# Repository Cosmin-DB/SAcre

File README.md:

# SAcre / SmartFeedbackDevice

Diseño electrónico de un dispositivo portátil basado en ESP32.

- Autor: Cosmin Dobrescu
- Herramienta: KiCad 10
- Proyecto principal: `sacre.kicad_pro`
- Estado: esquema y PCB corregidos; revisión digital completada (2026-09-13).
  Pendientes: aprobación física final, preparación del pedido y pruebas del prototipo.

## Mecanismo de trabajo

1. Leer este archivo completo antes de continuar una revisión.
2. Usar este README como única fuente de verdad. Las hipótesis nuevas del
   asistente se mantienen únicamente en `REVISION_PROVISIONAL.md` hasta que el
   autor las acepte o descarte; no crear otros informes auxiliares.
3. Mantener un identificador estable para cada incidencia.
4. Tratar toda incidencia inicialmente como una hipótesis, no como un fallo
   confirmado.
5. Intentar refutarla contrastando esquemático, PCB, símbolo, huella, datasheet
   y, cuando exista, evidencia del prototipo.
6. Registrar únicamente:
   - `Hipótesis`: afirmación que se comprueba.
   - `Evidencia`: datos concretos que sostienen el dictamen.
   - `Acción`: cambio exacto, solo si procede.
   - `Cierre`: comprobación necesaria para darlo por válido.
7. Usar estos estados:
   `PENDIENTE → CONFIRMADO / DESCARTADO / CONDICIONAL → CORREGIDO → VALIDADO`.
8. Durante la verificación no modificar el diseño.
9. La preparación de PCB autorizada el 2026-09-13 ya se completó. El enrutado
   y ajuste físico quedan al autor; cualquier nueva modificación de PCB por
   el asistente requiere un alcance autorizado. Comparar antes/después y no
   alterar cobre, contorno, conectores o keepout fuera de ese alcance.
10. Registrar por separado en cada incidencia:
    - `[ ] Esquemático corregido`
    - `[ ] PCB corregida y revisada por el autor`
11. Corregir únicamente incidencias `CONFIRMADO`; no corregir las
    `CONDICIONAL` sin resolver antes su condición.
12. Marcar `VALIDADO` solo después de aplicar el criterio de cierre y las
    comprobaciones ERC/DRC pertinentes.
13. Mantener separadas las mejoras preventivas de los fallos demostrados.
14. Evitar duplicar información y conservar las entradas breves, verificables
    y comprensibles sin contexto externo.
15. No volver a listar como trabajo pendiente una corrección ya aplicada.
    Distinguir revisión digital, aprobación del autor y prueba física; los
    datos de versiones antiguas deben identificarse como históricos.

## Fuentes para la verificación

Los datasheets recopilados están en `documentation/datasheets/`; se conservan
también los documentos útiles que ya estaban en `documentation/` y `RV-8803/`.
`bom_jlcpb.csv` identifica las piezas del prototipo anterior: sirve para
investigar sus fallos, no para pedir la nueva placa. Para fabricar, generar
el BOM desde el diseño actual usando sus campos `LCSC Part #`; ni los BOM
históricos ni las tablas resumidas de este documento sustituyen esa exportación.

| Bloque | Referencias cubiertas | Estado |
| --- | --- | --- |
| MCU y RF | ESP32-PICO-D4, guía de hardware ESP32, AN012400C00R3200 | Completo |
| Pantalla y táctil | GDEY042T81-T02, SSD1683, FT6336U, AFC24-S06FIC-00, AFC24-S24FIA-00 | Completo |
| USB, sensores y mando | CP2104, conector USB-C, LIS3DH, RV-8803-C7, pulsador | Completo |
| Alimentación y protección | TLV62568, TP4054, FHD4020S-470MT, FTC252012S1R0MBCA, BAT54C, MBR0530, SP0503BAHTG | Completo |
| Transistores y motor | CJ2312, CJ3415, SI1308EDL, UMH3N, S8050 | Completo para los componentes montados |

Selección actual de referencias críticas (incluye las sustituciones del prototipo):

| Ref. | Pieza seleccionada | LCSC |
| --- | --- | --- |
| Q2 | R+O S8050 | C20069125 |
| U5 | JSMSEMI TP4054 | C5381776 |
| L1 | cjiang FHD4020S-470MT | C843300 |
| L3 | cjiang FTC252012S1R0MBCA | C5832370 |
| Q4 | TECH PUBLIC SI1308EDL | C7603347 |
| D1, D8, D9 | JSCJ MBR0530 | C77336 |
| D2–D4 | onsemi MBR0530T3G | C236079 |
| D5 | R+O BAT54C | C22466350 |

Los documentos de MCP73831 y LQH44PN quedan solo como comparación: no
describen los componentes seleccionados para la nueva fabricación.

Auditoría de campos de compra: **85 componentes, 39 códigos distintos** con
`LCSC Part #` idéntico en esquema y PCB, incluida R28=`C21190` como R11.
No se añaden alias duplicados: Fabrication Toolkit, instalado en este equipo,
lee ese campo y lo exporta junto a `Designator`, `Footprint`, `Quantity` y
`Value`. Sincronizar esquema y PCB antes de exportar; comprobar códigos y
orientaciones en la previsualización de JLCPCB, no sólo la detección automática.
Chequeo del exportador y propuestas no aplicadas de reducción de variedad:
`REVISION_PROVISIONAL.md`, sección «BOM y posiciones de montaje» (2026-09-14).
Fuentes: [atributos del exportador](https://github.com/bennymeg/Fabrication-Toolkit#attributes)
y [guía KiCad de JLCPCB](https://jlcpcb.com/help/article/how-to-generate-the-bom-and-centroid-file-from-kicad).

H1–H4, J5, J6 y TP1 son elementos de PCB, sin referencia de compra y excluidos
del BOM. M1 se compra por AliExpress: excluido del BOM y del archivo de
posiciones de montaje en esquema y PCB; su huella y conexiones se conservan.
Quedan por confirmar modelo, corriente de arranque y encaje del motor.

Preparación del pedido (2026-09-14): JLCPCB emparejó correctamente las 85
referencias con los 39 códigos previstos para **4 placas ensambladas**. U2,
ESP32-PICO-D4 `C193707`, está clasificado como `Standard Only`, por lo que el
pedido debe usar **Standard PCBA, cara superior**. La propuesta de sustituir
R23/R24 por valores ya presentes reduciría dos alimentadores, pero fue
descartada por el autor: se conservan 24 kΩ/47 kΩ y 39 códigos. En la
previsualización, el autor corrigió manualmente sólo la orientación de Y1;
comprobarla otra vez en cualquier pedido futuro.

Stock consultado en la biblioteca de montaje JLCPCB el 2026-09-13:
39 referencias con existencias. AE1 tenía 8 unidades, pero el autor dispone
de acopio propio; Y1 tenía 2 y se acepta omitir el RTC si falta. SW1 tenía
970 unidades, cantidad aceptada por el autor. Reconfirmar disponibilidad al
pedir: la consulta no reserva piezas ni el stock de LCSC garantiza montaje
inmediato en JLCPCB. Preparar el pedido teniendo en cuenta el acopio y las
omisiones acordadas; no se ha cambiado ningún campo DNP del diseño.

## Fallos observados en el prototipo

Las correcciones indicadas ya están aplicadas al esquema y a la PCB.
Las casillas de aprobación del autor y las pruebas físicas siguen abiertas;
no significan que falte repetir el enrutado. La evidencia del fallo describe
la primera placa fabricada, no la versión actual.

- [ ] `TOUCH-01` SDA y SCL intercambiadas en el FPC táctil.
  - [x] Esquemático corregido: J1.1=`SCL` y J1.2=`SDA`.
  - [ ] PCB corregida y revisada por el autor.
  - `Estado`: CORREGIDO EN ESQUEMA Y PCB; prueba del táctil pendiente.
  - `Cierre`: comprobar detección del FT6336U y niveles/flancos de ambas
    señales con el flex conectado.
- [ ] `TOUCH-02` Revisar holgura, orientación y salida del flex táctil.
- [ ] `MOTOR-01` Incompatibilidad entre el pinout de Q2 y su huella.
  - [x] Esquemático corregido: Q2 es el S8050 SOT-23 montado, B1/E2/C3
    (`C20069125`).
  - [ ] PCB corregida y revisada por el autor.
  - `Estado`: CORREGIDO EN ESQUEMA Y PCB; validación del motor pendiente.
- [x] `TOUCH-03` Pull-up de la interrupción táctil descartado.
  - `Estado`: DESCARTADO; `INT_TOUCH` puede permanecer en GPIO35.
  - `Evidencia`: el FT6336U declara `INT` como E/S CMOS y no prescribe un
    pull-up externo. Verificar por medida sólo si aparecen flancos inestables.
- [ ] `PWR-02` El USB provoca arranque y ciclos rápidos de encendido/apagado.
  - `Estado`: CORREGIDO EN ESQUEMA Y PCB; validación del encendido pendiente.
  - `Hipótesis`: en el diseño fabricado U3 queda alimentado directamente por
    `USB_VBUS` mientras U2 está apagado. `TXD` llega sin aislamiento a `U0RXD`
    y `DTR/RTS` cruzan
    también hacia `EN/GPIO0` mediante Q7; cualquiera de esas vías puede
    realimentar parcialmente el ESP32 y `+3V3`. Esa tensión puede activar
    IO25/Q6 y el latch. Al caer de nuevo la alimentación, el USB repite el
    proceso.
  - `Evidencia`: en el diseño fabricado U3 está configurado como bus-powered;
    `TXD` y `U0RXD` están unidos directamente. Q7 contiene resistencias de base
    internas de 4,7 kΩ,
    pero no aísla un dominio alimentado de otro apagado. IO25 controla la
    puerta de Q6 mediante R18, Q6 tiene un umbral de 0,45–1 V y R14 sólo lo
    descarga con 100 kΩ. R13/C18 forman una constante de 30 ms. L2 puede
    agravar la caída, pero no explica el disparo inicial desde USB.
  - `Decisión`: U3 queda self-powered físicamente. `VDD`, `VIO` y `REGIN` van
    a `+3V3`; R23/R24=24 kΩ/47 kΩ detectan `USB_VBUS` sin realimentación;
    C23=1 µF y C20=0,1 µF desacoplan U3. C17=1 µF mejora `EN`.
    R13/C18 permanecen en 300 kΩ/100 nF; no se añade supervisor ni histéresis.
    El firmware debe activar IO25 pronto y puede exigir mantener el pulsador
    durante la programación.
  - `Cierre`: al conectar USB con el latch apagado, observar `VSYS`, `+3V3`,
    puerta de Q6 y puerta de Q5. Si `+3V3` sube antes que `VSYS`, queda
    confirmada la realimentación desde U3; repetir aislando `TXD` o forzando
    la puerta de Q6 a GND.
  - `Fuentes`: [CP2104, figura 9](documentation/cp2104-1397921.pdf),
    [ESP32-PICO-D4](documentation/datasheets/ESP32-PICO-series.pdf),
    [CJ2312](documentation/datasheets/CJ2312.pdf) y
    [circuito de referencia](https://circuitcellar.com/resources/quickbits/soft-latching-power-circuits/).
  - [x] Esquemático corregido.
  - [ ] PCB corregida y revisada por el autor.
- [ ] `MCU-01` Desacoplo externo local insuficiente en U2.
  - `Estado`: CORREGIDO EN ESQUEMA Y PCB; validación con radio/táctil pendiente.
  - `Hipótesis`: U2 depende de condensadores de `+3V3` alejados y carece del
    par externo recomendado junto al encapsulado.
  - `Evidencia`: el ESP32-PICO-D4 une a `VDD33` los pines 1 `VDDA`, 3 y 4
    `VDDA3P3`, 19 `VDD3P3_RTC` y 37 `VDD3P3_CPU`; su referencia añade
    10 µF + 0,1 µF externos. En la PCB, C17 es de `EN`; C22 está junto al
    regulador y C3/C4 desacoplan el LIS3DH. El SiP incorpora desacoplo interno,
    pero no elimina ese par externo.
  - `Acción`: añadidos C26=10 µF y C27=0,1 µF entre `+3V3` y GND, colocados
    junto al grupo 1/3/4 de U2. Conexión corta y ancha a U2.3/4, con vía GND
    a unos 1 mm del centro de C27.2. Los
    pines 19 y 37 deben quedar unidos por un plano o recorrido de baja
    impedancia; no se prescriben condensadores adicionales junto a ellos
    porque el PICO-D4 ya integra 0,1 µF en ambos dominios.
  - `Cierre`: comprobar colocación y retornos en PCB y medir `+3V3` junto a U2
    con Bluetooth y táctil simultáneos, sin caída por debajo de 3,0 V ni
    brownout.
  - `Fuente`: [ESP32-PICO-D4, figuras 7 y 10](documentation/datasheets/ESP32-PICO-series.pdf).
  - [x] Esquemático corregido.
  - [ ] PCB corregida y revisada por el autor.

## Correcciones aplicadas por bloques

Esquemático sincronizado y PCB enrutada por el autor. Las tareas abiertas
de estos bloques son de firmware o validación física, salvo indicación expresa.

### 1. GPIO, reset táctil y RTC

- [x] `RES_TOUCH_CTRL` en GPIO4; GPIO16 queda sin conexión externa, reservado
  para la flash interna del PICO-D4. JP1 eliminado. R11 y R28, ambas de 1 kΩ
  (`C21190`), están en paralelo: 500 Ω efectivos entre GPIO4 y RSTN.
  Mejora preventiva del nivel bajo sin añadir otra referencia al BOM;
  omitiendo R28 se recupera 1 kΩ. Ambas están previstas para montar.
  C25=10 µF a GND y D8 descarga el nodo al caer `+3V3`. Firmware:
  GPIO4 en drenador abierto, nivel bajo ≥60 ms, liberar sin conducir nivel alto
  y esperar ≥300 ms antes de usar I²C.
- [ ] Validar en prototipo el reset: nivel bajo calculado ≈0,47 V a 3,3 V
  con R11/R28, por debajo de 0,3·IOVCC. Mejora aplicada en esquema y PCB;
  prueba física pendiente. La secuencia de firmware no cambia.
- [x] `ACC_INT2` movida de GPIO12 a GPIO34; se conservan ambas interrupciones.
- [x] `RTC_INT` permanece en GPIO27 con R22=10 kΩ a `+3V3`.
- [x] `RTC_EVI` desconectada de GPIO15, R21=100 kΩ a `VBAT_RAW` y TP1.
- [x] Etiqueta huérfana `GPO` eliminada; GPIO32 queda libre.
- [x] Y1 alimentado directamente por `VBAT_RAW`, sin regulador añadido;
  C2=0,1 µF como desacoplo local.

- [x] Esquemático corregido.
- [ ] PCB corregida y revisada por el autor.

La aprobación final de encaje mecánico corresponde al autor.

### 2. USB, latch, C18 y EN

- [x] U3 alimentado desde `+3V3`; `USB_VBUS` detectado mediante
  R23/R24=24 kΩ/47 kΩ.
- [x] C23=1 µF y C20=0,1 µF locales; C24=4,7 µF/25 V en `VPP`.
- [x] C17=1 µF con R12=10 kΩ en `EN`.
- [x] R13/C18 conservados en 300 kΩ/100 nF; supervisor e histéresis descartados.
- [ ] Firmware integrado: activar IO25 pronto; mantener pulsado durante programación si
  el reset hace caer el latch. Requisito anotado junto al circuito del latch.
  Autosostén implementado en los ocho miniproyectos de `firmware/`;
  integración y prueba física pendientes.
- [x] Esquemático corregido.
- [ ] PCB corregida y revisada por el autor.

### 3. Regulador, ESP32, pantalla y motor

- [x] Pull-ups I²C R7/R8 cambiados de 10 kΩ a 5,1 kΩ para dar margen a
  400 kHz reutilizando el valor existente en el BOM.
- [x] ADP2108 sustituido por U6=`TLV62568DBVR` (`C163219`): buck de 1 A,
  salida nominal de 3,318 V con R26/R27=453 kΩ/100 kΩ. C31/C32=10 µF.
  Se elige por margen de corriente, disponibilidad y coste; el menor consumo
  en reposo y la salida fija del ADP2108 no justifican mantenerlo aquí.
- [x] `L3` fijada como
  [`FTC252012S1R0MBCA`](https://jlcpcb.com/partdetail/FTC252012S1R0MBCA/C5832370),
  LCSC `C5832370`: 1 µH, 4 A, Isat 5,6 A y DCR 35 mΩ. Huella de esquema
  `L_Changjiang_FTC252012S`; `C1042` queda solo como pieza histórica no válida.
  El campo `LCSC Part #` permite su selección automática en el BOM de JLCPCB.
- [x] C26=10 µF y C27=0,1 µF añadidos junto a U2 en el esquemático.
- [x] C26/C27 colocados y retornos revisados; C30 dispone de vía GND local.
- [x] Booster SSD1683 corregido en esquema: L1=47 µH, R10=2,2 Ω;
  C6 permanece en 4,7 µF/25 V; C8/C16 eliminados.
- [x] `L1` fijada como
  [`FHD4020S-470MT`](https://jlcpcb.com/partdetail/FHD4020S-470MT/C843300),
  LCSC `C843300`: 47 µH, 660 mA, Isat 1,3 A y DCR 950 mΩ. Huella de esquema
  `L_Changjiang_FNR4020S`. El campo `LCSC Part #` permite su selección
  automática en el BOM de JLCPCB.
- [x] Booster actualizado y revisado en PCB; Q4.2–R10.2 reducido a 2,34 mm.
  R9=1 MΩ entre GDR y GND, según la aplicación específica del panel.
- [x] Q2 corregido en esquema al pinout real B1/E2/C3 del S8050
  `C20069125`; se conservan R2=1 kΩ y D1.
- [x] Motor pasado de `+3V3` a `VSYS` mediante D9=MBR0530; `VMOTOR` alimenta
  M1, D1 y C1=0,1 µF. R25=100 kΩ mantiene la base de Q2 descargada. PWM
  opcional; encendido/apagado directo condicionado al motor indicado abajo.
- [x] Etapa dimensionada provisionalmente para el motor candidato: 3 V,
  rango 2,5–4 V y 70 mA nominales, suponiendo 90 mA de arranque. Confirmar
  este último dato en el motor comprado; no equivale a validación física.
- [ ] Confirmar modelo comprado, dimensiones/huella y corriente de arranque:
  no dar por corregido a 90 mA el dato ambiguo de 901 mA del anuncio.

### 4. Cargador y batería

- [x] C29=1 µF entre U5.4 `VDD` y GND y C28=10 µF entre U5.3 `VBAT` y
  GND añadidos y colocados junto a U5; retornos locales revisados en PCB.
- [x] R19=5,1 kΩ: unos 196 mA para la batería prevista de 600–700 mAh;
  reutiliza el mismo valor que R16/R17.
- [x] Protección integrada en la batería confirmada por el autor.
- [ ] Firmware integrado: habilitar la medida con GPIO26, leer `ADC_BATT`, deshabilitarla
  y apagar antes de ciclos repetidos de brownout. Requisito anotado en esquema;
  lectura implementada en `firmware/07_bateria`; umbral pendiente de medida.
- [x] Power-path descartado. U5 carga directamente `VBAT_RAW`; carga normal con
  el equipo apagado y encendido temporal permitido para programación.
- [x] Mantener TP4054 `C5381776`: LCSC/JLCPCB lo especifican a 4,2 V. La tabla
  ambigua del datasheet se conserva como cautela de validación, no como fallo
  que obligue a cambiar U5.

### 5. PCB y mecánica

Estado: **ENRUTADA Y REVISADA DIGITALMENTE** (2026-09-13), 93 componentes,
incluida R28 añadida y enrutada por el autor.

- [x] Sincronización, colocación y enrutado de las correcciones; revisión de
  desacoplos, retornos, GPIO y pinout de Q2. DRC sin conexiones pendientes.
- [x] Pista RF ajustada, J3 corregido a NPTH y vías separadas de la ranura.
- [x] Q4–R10 compactado; pasta bajo U2 conservada por decisión del autor.
  D6 no se mueve por la faja; U6 y SW1 se conservan según lo acordado.
- [ ] Comprobar físicamente flex de J1/pantalla, batería, motor y carcasa.
- [ ] Aprobar la PCB y preparar el pedido; ensayar el nuevo prototipo.

Histórico, no estado actual: `ae7a2bc` antes de preparar la PCB;
`92a95f1` colocación provisional; `0903610` enrutado y revisión final.
Las vistas [anterior](documentation/pcb_preparacion/antes.png),
[provisional](documentation/pcb_preparacion/despues.png) y de
[colocación](documentation/pcb_preparacion/colocacion.png) documentan sólo
la preparación inicial; no sirven como referencia de fabricación actual.

## Fabricación y cierre

### Configuración de fabricación — 2026-09-14

Enrutado completado por el autor y revisión digital final realizada.
La configuración de fabricación no cambia la geometría del circuito.

- Pedido objetivo: FR-4 estándar TG135, **4 capas, 1 mm nominal**, cobre
  exterior **1 oz** e interior **0,5 oz**, verde, serigrafía blanca, HASL con
  plomo y fresado normal. Sin prestaciones especiales añadidas.
- Montaje objetivo: **4 unidades, Standard PCBA, sólo cara superior**. U2
  `C193707` impide Economic PCBA. Confirmar el archivo de producción antes de
  fabricar; AE1 y Y1 se seleccionaron desde `My Parts` en el emparejamiento.
- Apilado: **JLC04101H-7628**. La consulta pública de JLCPCB para esos
  parámetros devuelve esta estructura tanto en «No requirement» como al
  seleccionarla explícitamente, con `fixedFee=0`, `coefficient=0` y fabricación
  rápida habilitada. Confirmar precio final en el pedido; no se ha comprado nada.
- KiCad conserva estos parámetros también en las variables de texto del
  proyecto. Elegir el apilado explícito en el pedido para evitar ambigüedad.

| Capa | Espesor configurado | Material / εr de referencia |
| --- | --- | --- |
| F.Mask / B.Mask | 0,0152 mm cada una | Verde / 3,8 |
| F.Cu / B.Cu | 0,035 mm cada una | Cobre exterior 1 oz |
| Dieléctrico 1 / 3 | 0,2104 mm cada uno | FR4 7628 / 4,4 |
| In1.Cu / In2.Cu | 0,0152 mm cada una | Cobre interior 0,5 oz, tras procesado |
| Dieléctrico 2 | 0,5000 mm | Núcleo FR4 / 4,6 nominal |

La estructura publicada suma 1,0212 mm sin máscara; con la máscara modelada,
KiCad muestra **1,0516 mm**. Se pide **1,0 mm nominal**, tolerancia estándar
±10 %. No ajustar artificialmente los dieléctricos para que la suma dé 1,000.

**Límite del modelo RF:** εr son referencias publicadas, no caracterización
del lote TG135. La calculadora actual de JLC usa NP-155F para 4–8 capas y
40,64 µm de cobre exterior, frente a los 35 µm de su tabla de apilado. El
cálculo de la pista RF indicado abajo utiliza el modelo de fabricación de
JLC; no se ha cambiado a TG155 ni simulado la antena completa. `tanδ=0,02`
se conserva como valor orientativo, no como dato confirmado del laminado.

DRC configurado: pista/separación absolutas ≥0,10 mm, cobre–borde ≥0,20 mm,
taladro de vía ≥0,20 mm, diámetro ≥0,40 mm y anular ≥0,05 mm. La regla de
`sacre.kicad_dru` exige diámetro ≥0,45 mm si el taladro es <0,30 mm para
evitar recargo por vías pequeñas. Se mantienen las separaciones de red de
0,15 mm y vías preferidas de 0,50/0,30 mm.
Apertura de máscara–cobre ajeno ≥0,09 mm; texto ≥1 mm y trazo ≥0,15 mm.
No se han cambiado las aperturas de máscara ni las exclusiones existentes.
Los límites específicos de ranuras, PTH y procesos no quedan todos cubiertos
por estas reglas globales: ver las condiciones de fabricación en
`REVISION_PROVISIONAL.md`.

**Resultado:** 0 conexiones pendientes, 0 diferencias con el esquema;
0 infracciones no excluidas y 18 exclusiones previas tras corregir J3 y
adaptar el límite de las vías pequeñas. Los tres errores de
cobre–ranura y los dos avisos de serigrafía fueron corregidos por el autor.
Límites reaplicados con KiCad cerrado y DRC repetido tras detectar que un
guardado posterior había restaurado las restricciones antiguas del proyecto.
U2.49: el autor conserva las ventanas de pasta y las 16 vías recolocadas.
«Plugged» no garantiza el sellado de vías dentro del pad; se acepta esta
limitación sin añadir relleno epoxi/cobre. Calidad de soldadura pendiente
de validar; no es una recolocación o modificación de pasta pendiente.

Fuentes: [apilados JLCPCB](https://jlcpcb.com/impedance),
[capacidades](https://jlcpcb.com/capabilities/pcb-capabilities),
[modelo de cálculo](https://jlcpcb.com/help/article/user-guide-to-the-jlcpcb-impedance-calculator)
y [tratamiento de vías](https://jlcpcb.com/help/article/pcb-via-covering).

### Pista RF — ajuste autorizado el 2026-09-13 (`RV-11`)

- `/ANT_RF`: ancho **0,26 mm** en sus tres segmentos y dos arcos; recorrido,
  huella de antena, meandro y máscara sin cambios. Zonas rellenadas; separación
  lateral a GND ≈0,1505 mm y plano In1 continuo bajo la pista externa.
- Modelo JLC `CoatedCoplanarWaveguideWithLowerGnd1B`: H=0,2104 mm, εr=4,4,
  cobre acabado=40,64 µm, ancho superior 12,7 µm menor que el inferior;
  máscara εr=3,8, 25,4 µm sobre sustrato y 15,24 µm sobre cobre. Son los
  parámetros actuales del servicio, no todos coinciden con su página de ayuda.
- Resultado nominal con hueco lateral de 0,15 mm: **50,15 Ω** para 0,26 mm,
  frente a 44,87 Ω para el ancho anterior de 0,3341 mm. La aproximación previa
  sin máscara de 50,8 Ω queda sustituida por este contraste más completo.
- Este cálculo no valida la impedancia del lote TG135 ni la adaptación/alcance
  de la antena completa. Recalcular si cambian apilado, cobre, máscara, ancho,
  separación a masa o plano de referencia. Recordatorio junto a AE1 en
  `Cmts.User`, fuera del contorno; no forma parte de la serigrafía.
- [ ] PCB revisada visualmente por el autor; validación RF física pendiente.
- Fuente: [calculadora JLCPCB](https://jlcpcb.com/pcb-impedance-calculator).

### Checklist de cierre

- Revisión final de PCB (2026-09-13): 0 conexiones pendientes, 0 diferencias
  con el esquema y 0 infracciones no excluidas tras ajustar las reglas de vía;
  se mantienen 18 exclusiones previas. Q4–R10 ya corregido; pasta de U2 conservada por
  decisión del autor. Gerber/taladros revisados en `tmp/final-review-fab/`,
  no publicados como fabricación definitiva. Resultado y límites en
  `REVISION_PROVISIONAL.md`, «Cierre de revisión sobre el guardado actual».
- `RV-15`: agujeros de posicionamiento de J3 corregidos a NPTH de 0,70 mm
  en PCB y biblioteca; posiciones y anclajes soldados intactos. DRC sin
  infracciones nuevas por este cambio; revisión visual del autor pendiente.

Las siguientes casillas son el cierre humano o experimental, no correcciones
eléctricas obligatorias abiertas:

- [ ] `PWR-01` Medir alimentación, carga y encendido/apagado sin bucles.
- [ ] `USB-01` Probar enumeración y programación, incluido el autosostén.
- [ ] `MCU-02` Probar arranque/reset y coexistencia de táctil y Bluetooth.
- [ ] `DISP-01` Probar refresco y tensiones auxiliares de la pantalla.
- [ ] `SENS-01` Probar sensores/RTC y calibrar el umbral de batería baja.
- [ ] `RF-01` Validar alcance de radio; el cálculo de pista ya está realizado.
- [ ] `PCB-01` Aprobación visual final del autor; revisión digital completada.
- [ ] `MECH-01` Confirmar encaje, alturas, flex y accesibilidad.
- [ ] `FAB-01` Aprobar exclusiones DRC y avisos ERC, comprobar BOM/posiciones
  y stock del pedido, regenerar/revisar el paquete definitivo y confirmar CAM.
  ERC: 122 desajustes de símbolos y aviso de AE1.2, conectado a GND;
  no se declara limpio ni se actualizan bibliotecas a ciegas.

## Uso

Pruebas independientes para el hardware actual: [firmware/README.md](firmware/README.md).
Ocho proyectos PlatformIO, uno por periférico/función, con autosostén del latch
común. Incluyen mapa GPIO y criterios de prueba; validación física pendiente.

Abrir `sacre.kicad_pro`. Las librerías, huellas y modelos 3D del diseño están
incluidos en el repositorio; el estado de los datasheets figura arriba.

Cualquier exportación local en `production/` debe considerarse desactualizada
hasta completar `FAB-01`.

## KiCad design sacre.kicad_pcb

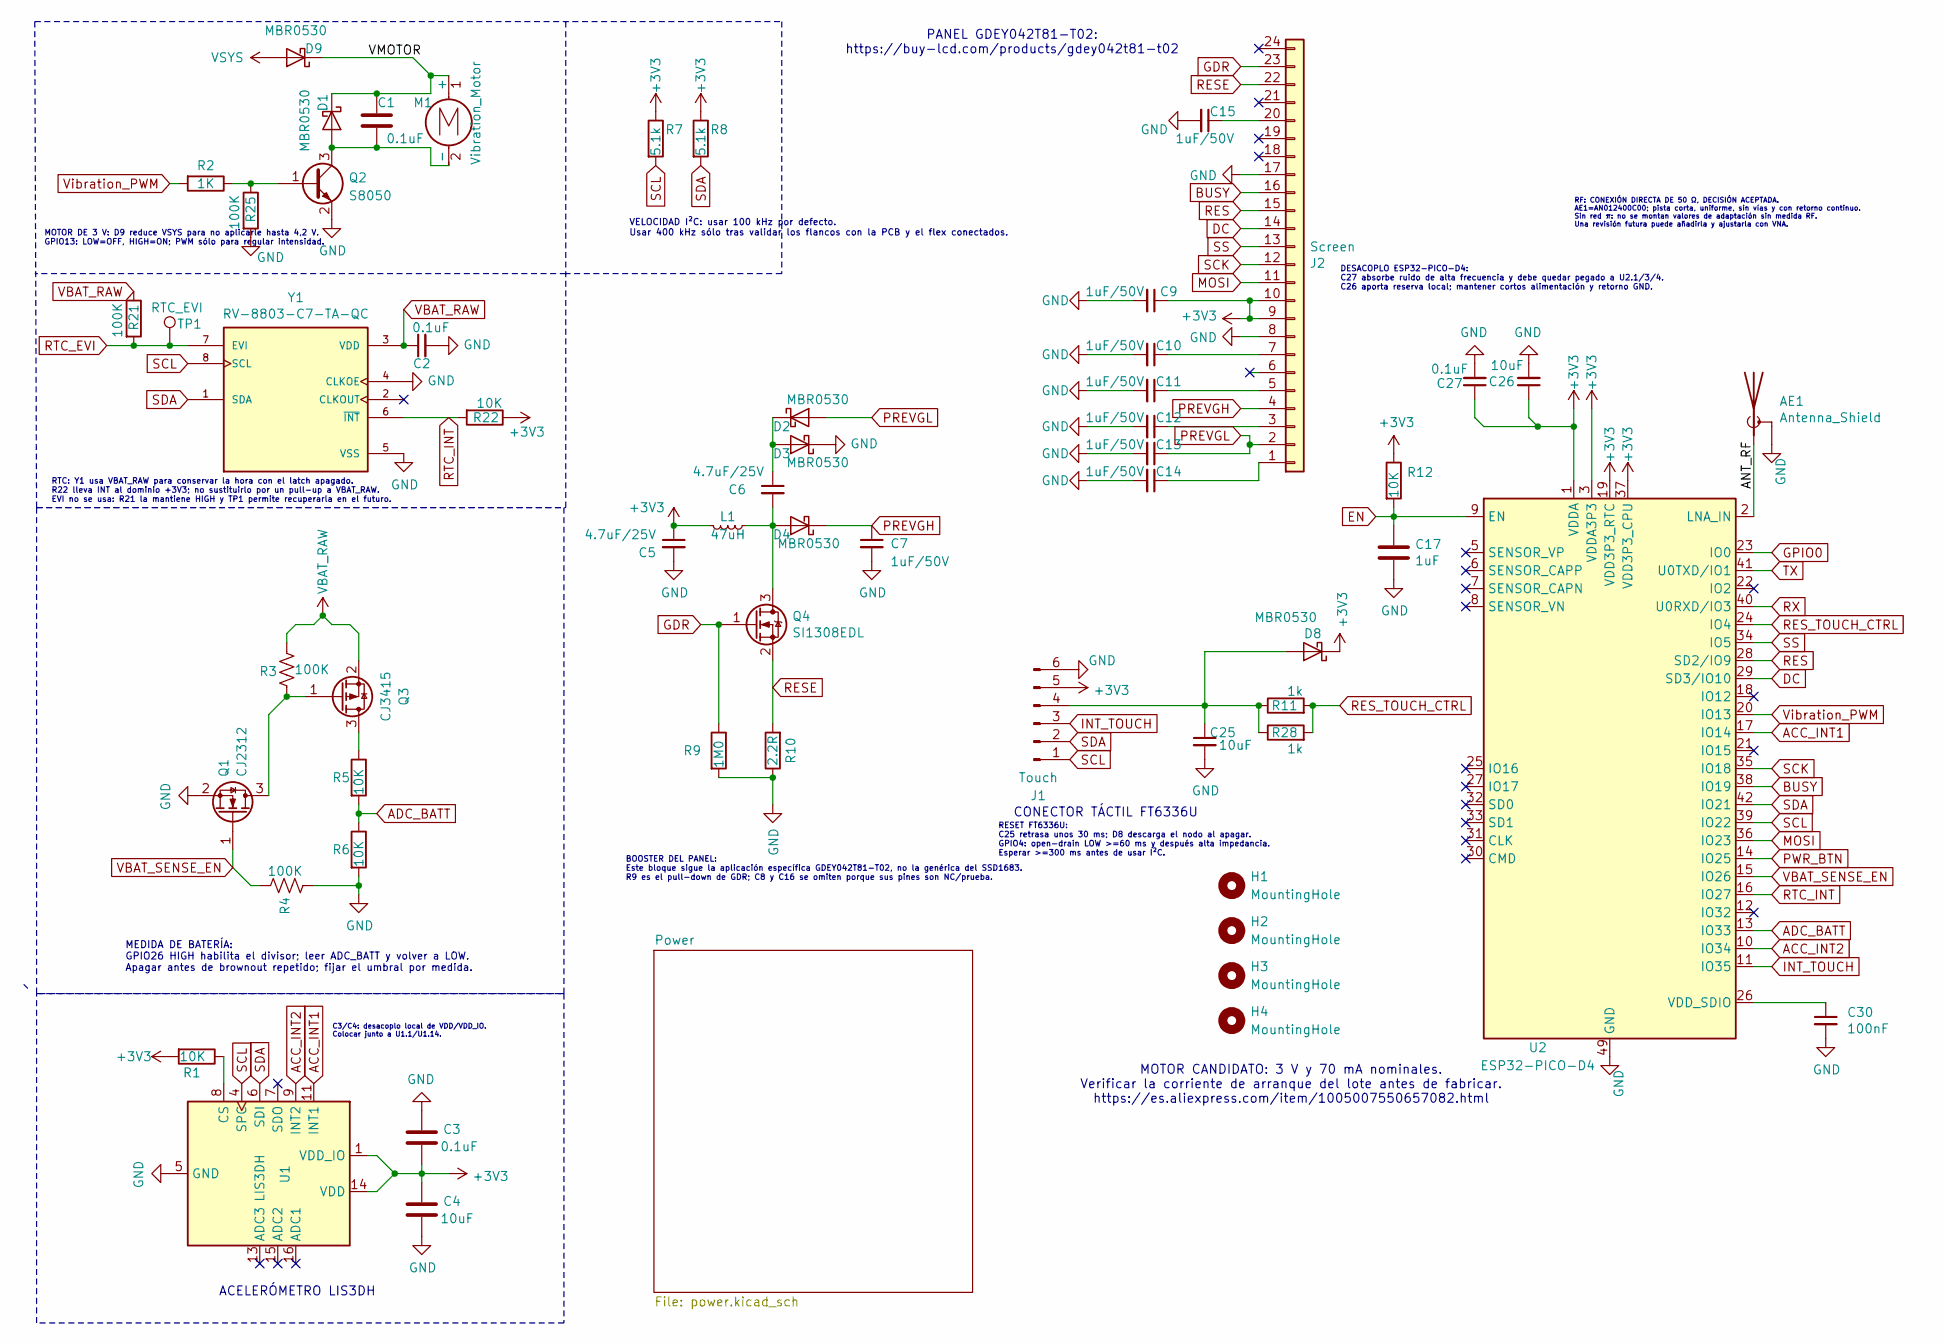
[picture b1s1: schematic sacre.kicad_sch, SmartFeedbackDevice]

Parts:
AE1: Antenna_Shield; AN012400C00R3200; LCSC Part # C5943777
C1, C2, C3, C27: 0.1uF; C_0603_1608Metric; LCSC Part # C14663
C4, C25, C26: 10uF; C_0603_1608Metric; LCSC Part # C19702
C5, C6: 4.7uF/25V; C_0603_1608Metric; LCSC Part # C69335
C7, C9, C10, C11, C12, C13, C14, C15: 1uF/50V; C_0603_1608Metric; LCSC Part # C15849
C17: 1uF; C_0603_1608Metric; LCSC Part # C15849
C30: 100nF; C_0603_1608Metric; LCSC Part # C14663
D1, D8, D9: MBR0530; D_SOD-123; LCSC Part # C77336
D2, D3, D4: MBR0530; D_SOD-123; LCSC Part # C236079
H1, H2, H3, H4: MountingHole; MountingHole_2.7mm_M2.5
J1: Touch; FPC-SMD_P0.50-6P_QCHF-SM-H2.0; LCSC Part # C262287
J2: Screen; FPC-SMD_P0.50-24P_QCHF-SM-H2.0; LCSC Part # C262683
L1: 47uH; L_Changjiang_FNR4020S; MPN FHD4020S-470MT; LCSC Part # C843300
M1: Vibration_Motor; C_1206_3216Metric
Q1: CJ2312; SOT-23; LCSC Part # C23521
Q2: S8050; SOT-23; LCSC Part # C20069125
Q3: CJ3415; SOT-23; LCSC Part # C2910186
Q4: SI1308EDL; SOT-323_SC-70; LCSC Part # C7603347
R1, R5, R6, R12, R22: 10K; R_0603_1608Metric; LCSC Part # C25804
R2: 1K; R_0603_1608Metric; LCSC Part # C21190
R3, R4, R21, R25: 100K; R_0603_1608Metric; LCSC Part # C25803
R7, R8: 5.1k; R_0603_1608Metric; LCSC Part # C23186
R9: 1M0; R_0603_1608Metric; LCSC Part # C22935
R10: 2.2R; R_0603_1608Metric; LCSC Part # C22939
R11, R28: 1k; R_0603_1608Metric; LCSC Part # C21190
TP1: RTC_EVI; TestPoint_Pad_D1.0mm
U1: LIS3DH; LGA-16_3x3mm_P0.5mm_LayoutBorder3x5y; LCSC Part # C15134
U2: ESP32-PICO-D4; QFN-48-1EP_7x7mm_P0.5mm_EP3.5x3.5mm; LCSC Part # C193707
Y1: RV-8803-C7-TA-QC; MICROCRYSTAL_RV-8803-C7-TA-QC; PARTREV 2.0; LCSC Part # C2846926

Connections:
+3V3: C3.2, C4.1, C5.1, C9.1, C26.1, C27.1, D8.1 (K), J1.5, J2.9, J2.10, L1.2, R1.2, R7.1, R8.1, R12.1, R22.1, U1.1 (VDD_IO), U1.14 (VDD), U2.1 (VDDA), U2.3 (VDDA3P3), U2.4 (VDDA3P3), U2.19 (VDD3P3_RTC), U2.37 (VDD3P3_CPU), U2.43 (VDDA), U2.46 (VDDA); also elsewhere on the board
/ANT_RF: AE1.1 (A), U2.2 (LNA_IN)
/VMOTOR: C1.1, D1.1 (K), D9.1 (K), M1.1 (+)
ACC_INT1: U1.11 (INT1), U2.17 (IO14)
ACC_INT2: U1.9 (INT2), U2.10 (IO34)
ADC_BATT: R5.2, R6.1, U2.13 (IO33)
BUSY: J2.16, U2.38 (IO19)
DC: J2.14, U2.29 (SD3/IO10)
EN: C17.1, R12.2, U2.9 (EN); also elsewhere on the board
GDR: J2.23, Q4.1 (G), R9.1
GND: AE1.2 (Shield), C2.2, C3.1, C4.2, C5.2, C7.2, C9.2, C10.2, C11.2, C12.2, C13.2, C14.2, C15.2, C17.2, C25.2, C26.2, C27.2, C30.2, D3.1 (K), J1.6, J2.8, J2.17, Q1.2 (S), Q2.2 (E), R4.1, R6.2, R9.2, R10.1, R25.2, U1.5 (GND), U1.10 (GND), U1.12 (GND), U2.49 (GND), Y1.4 (CLKOE), Y1.5 (VSS); also elsewhere on the board
GPIO0: U2.23 (IO0); also elsewhere on the board
INT_TOUCH: J1.3, U2.11 (IO35)
MOSI: J2.11, U2.36 (IO23)
unnamed: C1.2, D1.2 (A), M1.2 (-), Q2.3 (C)
unnamed: C6.1, D2.1 (K), D3.2 (A)
unnamed: C6.2, D4.2 (A), L1.1, Q4.3 (D)
unnamed: C25.1, D8.2 (A), J1.4, R11.1, R28.1
unnamed: C14.1, J2.1
unnamed: C12.1, J2.3
unnamed: C11.1, J2.5
unnamed: C10.1, J2.7
unnamed: C15.1, J2.20
unnamed: Q1.3 (D), Q3.1 (G), R3.1
unnamed: Q2.1 (B), R2.1, R25.1
unnamed: Q3.3 (D), R5.1
unnamed: R1.1, U1.8 (CS)
unnamed: C30.1, U2.26 (VDD_SDIO)
PREVGH: C7.1, D4.1 (K), J2.4
PREVGL: C13.1, D2.2 (A), J2.2
PWR_BTN: U2.14 (IO25); also elsewhere on the board
RES: J2.15, U2.28 (SD2/IO9)
RESE: J2.22, Q4.2 (S), R10.2
RES_TOUCH_CTRL: R11.2, R28.2, U2.24 (IO4)
RTC_EVI: R21.2, TP1.1 (1_1), Y1.7 (EVI)
RTC_INT: R22.2, U2.16 (IO27), Y1.6 (~INT)
RX: U2.40 (U0RXD/IO3); also elsewhere on the board
SCK: J2.12, U2.35 (IO18)
SCL: J1.1, R7.2, U1.4 (SPC), U2.39 (IO22), Y1.8 (SCL)
SDA: J1.2, R8.2, U1.6 (SDI), U2.42 (IO21), Y1.1 (SDA)
SS: J2.13, U2.34 (IO5)
TX: U2.41 (U0TXD/IO1); also elsewhere on the board
VBAT_RAW: C2.1, Q3.2 (S), R3.2, R21.1, Y1.3 (VDD); also elsewhere on the board
VBAT_SENSE_EN: Q1.1 (G), R4.2, U2.15 (IO26)
VSYS: D9.2 (A); also elsewhere on the board
Vibration_PWM: R2.2, U2.20 (IO13)

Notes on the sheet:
ACELERÓMETRO LIS3DH
C3/C4: desacoplo local de VDD/VDD_IO. Colocar junto a U1.1/U1.14.
MEDIDA DE BATERÍA: GPIO26 HIGH habilita el divisor; leer ADC_BATT y volver a LOW. Apagar antes de brownout repetido; fijar el umbral por medida.
RF: CONEXIÓN DIRECTA DE 50 Ω, DECISIÓN ACEPTADA. AE1=AN012400C00; pista corta, uniforme, sin vías y con retorno continuo. Sin red π: no se montan valores de adaptación sin medida RF. Una revisión futura puede añadirla y ajustarla con VNA.
CONECTOR TÁCTIL FT6336U
MOTOR CANDIDATO: 3 V y 70 mA nominales. Verificar la corriente de arranque del lote antes de fabricar. https://es.aliexpress.com/item/1005007550657082.html
VELOCIDAD I²C: usar 100 kHz por defecto. Usar 400 kHz sólo tras validar los flancos con la PCB y el flex conectados.
RTC: Y1 usa VBAT_RAW para conservar la hora con el latch apagado. R22 lleva INT al dominio +3V3; no sustituirlo por un pull-up a VBAT_RAW. EVI no se usa: R21 la mantiene HIGH y TP1 permite recuperarla en el futuro.
DESACOPLO ESP32-PICO-D4: C27 absorbe ruido de alta frecuencia y debe quedar pegado a U2.1/3/4. C26 aporta reserva local; mantener cortos alimentación y retorno GND.
PANEL GDEY042T81-T02: https://buy-lcd.com/products/gdey042t81-t02
MOTOR DE 3 V: D9 reduce VSYS para no aplicarle hasta 4,2 V. GPIO13: LOW=OFF, HIGH=ON; PWM sólo para regular intensidad.
BOOSTER DEL PANEL: Este bloque sigue la aplicación específica GDEY042T81-T02, no la genérica del SSD1683. R9 es el pull-down de GDR; C8 y C16 se omiten porque sus pines son NC/prueba.
RESET FT6336U: C25 retrasa unos 30 ms; D8 descarga el nodo al apagar. GPIO4: open-drain LOW >=60 ms y después alta impedancia. Esperar >=300 ms antes de usar I²C.

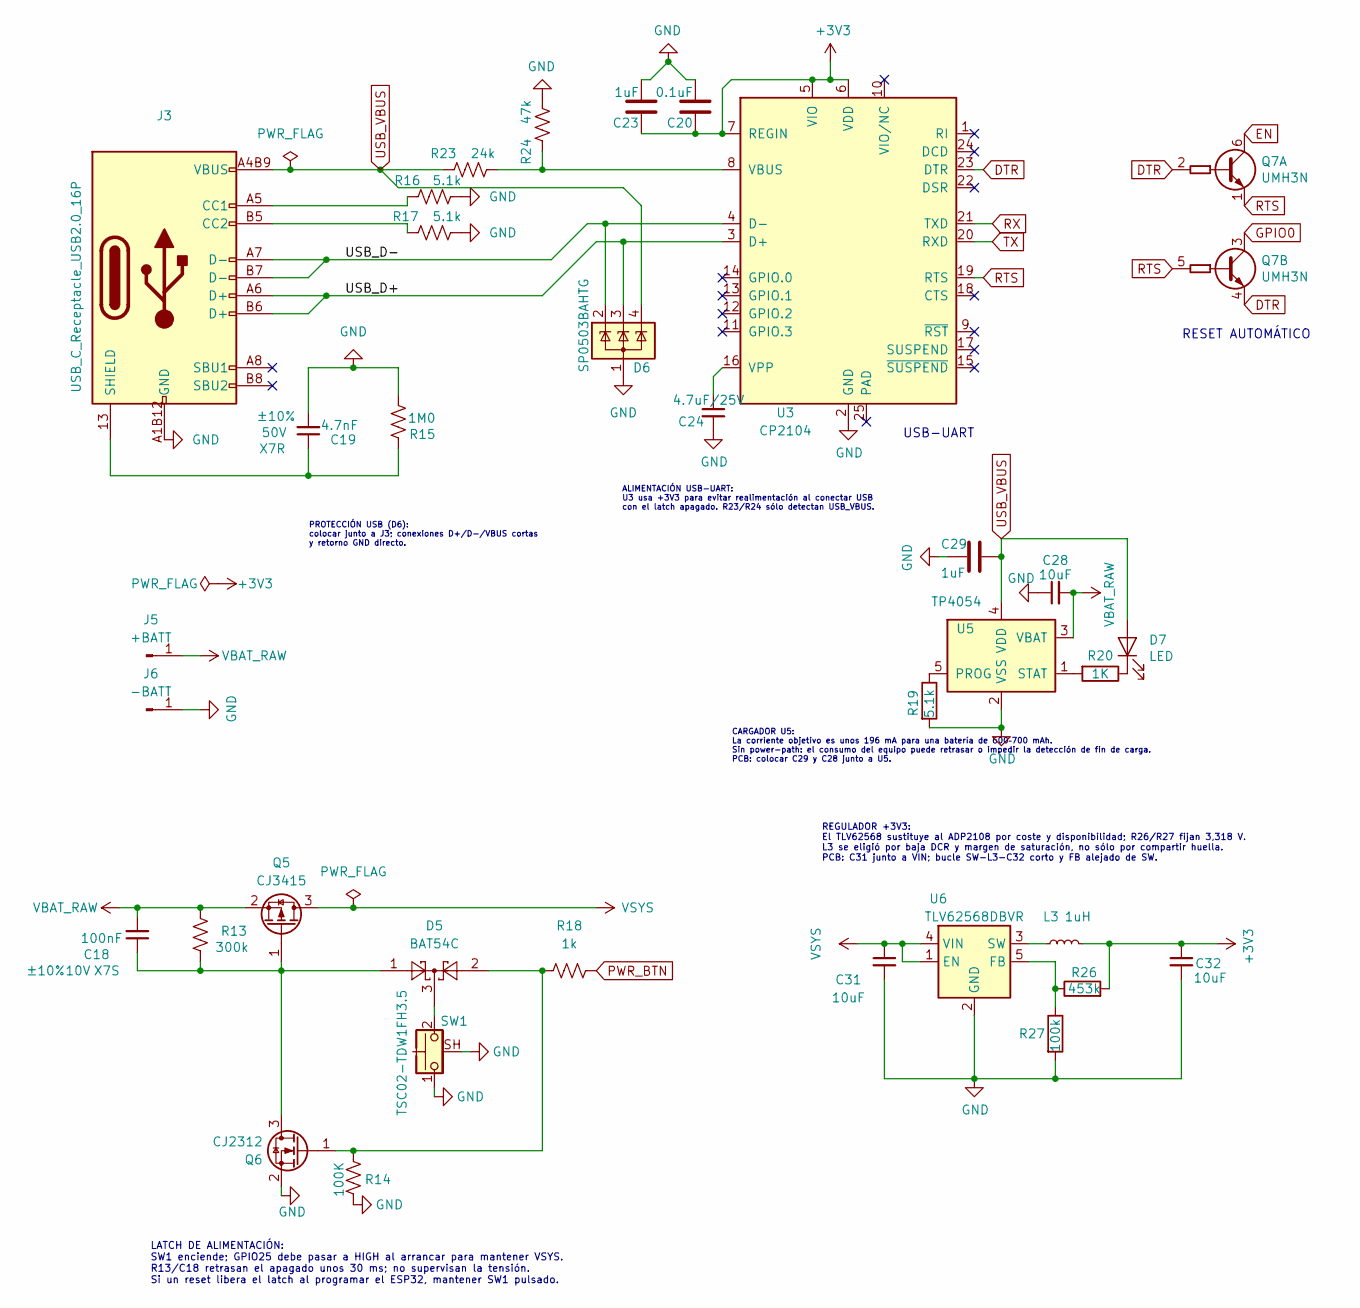
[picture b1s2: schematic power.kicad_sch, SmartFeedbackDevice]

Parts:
C18: 100nF; C_0402_1005Metric; Tolerance ±10%; Voltage_Rated 10V; LCSC Part # C1525
C19: 4.7nF; C_0603_1608Metric; Tolerance ±10%; Voltage_Rated 50V; LCSC Part # C53987
C20: 0.1uF; C_0603_1608Metric; LCSC Part # C14663
C23, C29: 1uF; C_0603_1608Metric; LCSC Part # C15849
C24: 4.7uF/25V; C_0603_1608Metric; LCSC Part # C69335
C28, C31, C32: 10uF; C_0603_1608Metric; LCSC Part # C19702
D5: BAT54C; SOT-23; LCSC Part # C22466350
D6: SP0503BAHTG; SOT-143; LCSC Part # C3040626
D7: LED; LED_1206_3216Metric_Pad1.42x1.75mm_HandSolder; LCSC Part # C84270
J3: USB_C_Receptacle_USB2.0_16P; USB-C-SMD_TYPE-C-16PIN-2MD-073; LCSC Part # C2765186
J5: +BATT; SolderWirePad_1x01_SMD_3x6mm
J6: -BATT; SolderWirePad_1x01_SMD_3x6mm
L3: 1uH; L_Changjiang_FTC252012S; MPN FTC252012S1R0MBCA; LCSC Part # C5832370
Q5: CJ3415; SOT-23; LCSC Part # C2910186
Q6: CJ2312; SOT-23; LCSC Part # C23521
Q7: UMH3N; SOT-363_SC-70-6; LCSC Part # C62892
R13: 300k; R_0603_1608Metric; LCSC Part # C23024
R14: 100K; R_0603_1608Metric; LCSC Part # C25803
R15: 1M0; R_0603_1608Metric; LCSC Part # C22935
R16, R17, R19: 5.1k; R_0603_1608Metric; LCSC Part # C23186
R18: 1k; R_0603_1608Metric; LCSC Part # C21190
R20: 1K; R_0603_1608Metric; LCSC Part # C21190
R23: 24k; R_0603_1608Metric; LCSC Part # C23352
R24: 47k; R_0603_1608Metric; LCSC Part # C25819
R26: 453k; R_0603_1608Metric; MPN RT0603BRD07453KL; LCSC Part # C861412
R27: 100k; R_0603_1608Metric; LCSC Part # C25803
SW1: TSC02-TDW1FH3.5; SW-SMD_L7.8-W3.5-P4.20-EH; LCSC Part # C22362983
U3: CP2104; QFN-24-1EP_4x4mm_P0.5mm_EP2.6x2.6mm; LCSC Part # C47742
U5: TP4054; SOT-23-5; LCSC Part # C5381776
U6: TLV62568DBVR; SOT-23-5; MPN TLV62568DBVR; LCSC Part # C163219

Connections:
+3V3: C20.1, C23.1, C32.1, L3.2, R26.2, U3.5 (VIO), U3.6 (VDD), U3.7 (REGIN); also elsewhere on the board
/Power/USB_D+: D6.3 (K), J3.A6 (D+), J3.B6 (D+), U3.3 (D+)
/Power/USB_D-: D6.2 (K), J3.A7 (D-), J3.B7 (D-), U3.4 (D-)
DTR: Q7.2 (B1), Q7.4 (E2), U3.23 (DTR)
EN: Q7.6 (C1); also elsewhere on the board
GND: C19.2, C20.2, C23.2, C24.2, C28.1, C29.2, C31.2, C32.2, D6.1 (A), J3.A1B12 (GND), J3.B1A12 (GND), J6.1 (Pin_1_1), Q6.2 (S), R14.2, R15.2, R16.2, R17.2, R19.2, R24.2, R27.2, SW1.1, SW1.SH (B), U3.2 (GND), U5.2 (VSS), U6.2 (GND); also elsewhere on the board
GPIO0: Q7.3 (C2); also elsewhere on the board
unnamed: D5.3, SW1.2
unnamed: D7.1 (K), R20.1
unnamed: J3.A5 (CC1), R16.1
unnamed: J3.B5 (CC2), R17.1
unnamed: C19.1, J3.13 (SHIELD), J3.14 (GND), R15.1
unnamed: C18.1, D5.1, Q5.1 (G), Q6.3 (D), R13.2
unnamed: D5.2, Q6.1 (G), R14.1, R18.1
unnamed: R23.2, R24.1, U3.8 (VBUS)
unnamed: C24.1, U3.16 (VPP)
unnamed: R19.1, U5.5 (PROG)
unnamed: R20.2, U5.1 (STAT)
unnamed: R26.1, R27.1, U6.5 (FB)
unnamed: L3.1, U6.3 (SW)
PWR_BTN: R18.2; also elsewhere on the board
RTS: Q7.1 (E1), Q7.5 (B2), U3.19 (RTS)
RX: U3.21 (TXD); also elsewhere on the board
TX: U3.20 (RXD); also elsewhere on the board
USB_VBUS: C29.1, D6.4 (K), D7.2 (A), J3.A4B9 (VBUS), J3.B4A9 (VBUS), R23.1, U5.4 (VDD)
VBAT_RAW: C18.2, C28.2, J5.1 (Pin_1_1), Q5.2 (S), R13.1, U5.3 (VBAT); also elsewhere on the board
VSYS: C31.1, Q5.3 (D), U6.1 (EN), U6.4 (VIN); also elsewhere on the board

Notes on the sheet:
RESET AUTOMÁTICO
ALIMENTACIÓN USB-UART: U3 usa +3V3 para evitar realimentación al conectar USB con el latch apagado. R23/R24 sólo detectan USB_VBUS.
USB-UART
PROTECCIÓN USB (D6): colocar junto a J3; conexiones D+/D-/VBUS cortas y retorno GND directo.
LATCH DE ALIMENTACIÓN: SW1 enciende; GPIO25 debe pasar a HIGH al arrancar para mantener VSYS. R13/C18 retrasan el apagado unos 30 ms; no supervisan la tensión. Si un reset libera el latch al programar el ESP32, mantener SW1 pulsado.
REGULADOR +3V3: El TLV62568 sustituye al ADP2108 por coste y disponibilidad; R26/R27 fijan 3,318 V. L3 se eligió por baja DCR y margen de saturación, no sólo por compartir huella. PCB: C31 junto a VIN; bucle SW-L3-C32 corto y FB alejado de SW.
CARGADOR U5: La corriente objetivo es unos 196 mA para una batería de 600–700 mAh. Sin power-path: el consumo del equipo puede retrasar o impedir la detección de fin de carga. PCB: colocar C29 y C28 junto a U5.

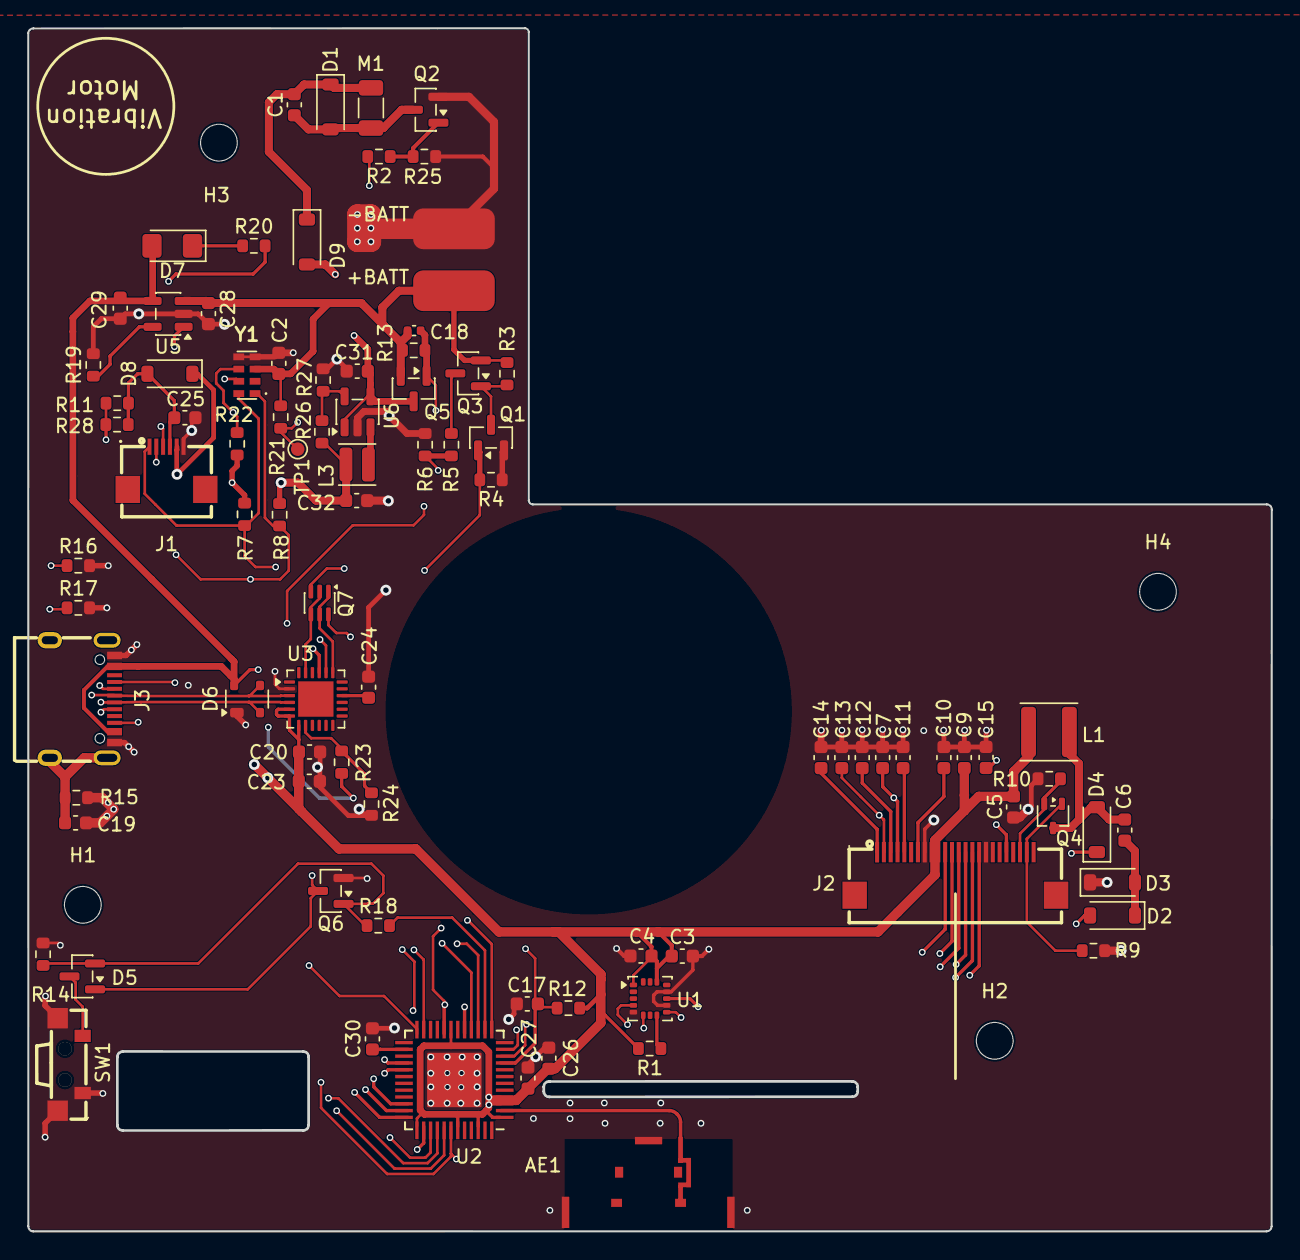
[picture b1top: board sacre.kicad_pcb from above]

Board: 4 copper layers, 91.4 x 88.4 mm, 93 parts (0 on the bottom side), 64 nets.

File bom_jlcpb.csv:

Comment;Designator;Footprint;JLCPCB Part #;Qty;Ext.Price($)
USB_C_Receptacle_USB2.0_16P;J3;USB-C-SMD_TYPE-C-16PIN-2MD-073;C2765186;3;0.20
RV-8803-C7-TA-QC;Y1;MICROCRYSTAL_RV-8803-C7-TA-QC;C2846926;2;0.00
MBR0530;D1,D2,D3,D4;D_SOD-123;C77336;12;0.40
Touch;J1;FPC-SMD_P0.50-6P_QCHF-SM-H2.0;C262287;4;0.57
SI1308EDL;Q4;SOT-323_SC-70;C7603347;6;0.54
1uH;L2;0805;C1042;20;0.82
TP4054;U5;SOT-23-5;C5381776;10;0.15
CJ3415;Q3,Q5;SOT-23;C2910186;8;0.42
0.1uF;C17,C3;0603;C14663;20;0.06
0.47R;R10;0603;C23411;20;0.09
LIS3DH;U1;LGA-16_3x3mm_P0.5mm_LayoutBorder3x5y;C15134;2;2.03
TSC02-TDW1FH3.5;SW1;SW-SMD_L7.8-W3.5-P4.20-EH;C22362983;5;0.12
SP0503BAHTG;D6;SOT-143;C3040626;5;0.48
ESP32-PICO-D4;U2;QFN-48-1EP_7x7mm_P0.5mm_EP3.5x3.5mm;C193707;2;8.51
4.7uF/25V;C5,C6;0603;C69335;20;0.34
CP2104;U3;QFN-24-1EP_4x4mm_P0.5mm_EP2.6x2.6mm;C47742;2;4.48
10uF;C2,C21,C22,C4;0603;C19702;20;0.20
10uH/1A;L1;L_Vishay_IFSC-1515AH_4x4x1.8mm;C602032;5;0.31
UMH3N;Q7;SOT-363_SC-70-6;C62892;6;0.29
CJ2312;Q1,Q6;SOT-23;C23521;8;0.34
5.1k;R16,R17;0603;C23186;20;0.03
BAT54C;D5;SOT-23;C22466350;10;0.14
100nF;C18;0402;C1525;20;0.03
Screen;J2;FPC-SMD_P0.50-24P_QCHF-SM-H2.0;C262683;2;0.32
1M0;R15;0603;C22935;20;0.03
1uF;C10,C11,C12,C13,C14,C15,C16,C7,C8,C9,C1,C20;0603;C15849;34;0.26
ADP2108AUJ-3.3;U4;TSOT-23-5;C143875;2;0.00
10K;R1,R11,R12,R19,R5,R6,R7,R8,R9;0603;C25804;28;0.04
1k;R18,R2,R20;0603;C21190;20;0.03
S8050;Q2;SOT-23;C20069125;10;0.10
100K;R14,R3,R4;0603;C25803;20;0.04
300k;R13;0603;C23024;20;0.03
4.7nF;C19;0603;C53987;20;0.06
LED;D7;1206;C84270;15;0.35

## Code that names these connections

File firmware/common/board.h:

#pragma once
#include <Arduino.h>
#include <esp_system.h>

// GPIO numbers, NOT package pin numbers. Checked against sacre.kicad_sch
// netlist and PCB on 2026-09-14. ESP32-PICO-D4; GPIO16 is internal flash.
namespace Pins {
constexpr uint8_t LATCH = 25;
constexpr uint8_t MOTOR = 13;
constexpr uint8_t BAT_ENABLE = 26;
constexpr uint8_t BAT_ADC = 33;
constexpr uint8_t SDA = 21, SCL = 22;
constexpr uint8_t TOUCH_RESET = 4, TOUCH_INT = 35;
constexpr uint8_t ACC_INT1 = 14, ACC_INT2 = 34;
constexpr uint8_t RTC_INT = 27;
constexpr uint8_t EPD_CS = 5, EPD_DC = 10, EPD_RESET = 9;
constexpr uint8_t EPD_BUSY = 19, EPD_SCK = 18, EPD_MOSI = 23;
}

namespace Board {
inline void begin(const char* test) {
  // First app action: self-hold, before Serial, I2C, SPI or radio.
  digitalWrite(Pins::LATCH, HIGH);
  pinMode(Pins::LATCH, OUTPUT);
  digitalWrite(Pins::MOTOR, LOW);
  pinMode(Pins::MOTOR, OUTPUT);
  digitalWrite(Pins::BAT_ENABLE, LOW);
  pinMode(Pins::BAT_ENABLE, OUTPUT);
  // Release touch reset; the external RC supplies the high level.
  pinMode(Pins::TOUCH_RESET, INPUT);
  digitalWrite(Pins::EPD_CS, HIGH);
  pinMode(Pins::EPD_CS, OUTPUT);
  Serial.begin(115200);
  delay(200);
  Serial.printf("\nSAcre / %s / reset reason=%d\n", test, int(esp_reset_reason()));
  Serial.println("GPIO25 HIGH. x: apagar (soltar antes el boton).");
}

[[noreturn]] inline void powerOff() {
  digitalWrite(Pins::MOTOR, LOW);
  digitalWrite(Pins::BAT_ENABLE, LOW);
  Serial.println("Apagando. Si sigue encendida, soltar el boton.");
  Serial.flush();
  digitalWrite(Pins::LATCH, LOW);
  for (;;) delay(1000); // Do not restart/reassert the latch if power persists.
}

inline int command() {
  if (!Serial.available()) return -1;
  const int c = Serial.read();
  if (c == 'x') powerOff();
  return c;
}

[[noreturn]] inline void fail(const char* message) {
  Serial.printf("ERROR: %s. Corregir y reiniciar; x: apagar.\n", message);
  for (;;) { command(); delay(10); }
}
}

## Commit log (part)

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2026-05-08 Clean KiCad project files
2026-05-08 Fix KiCad schematic symbol name
2026-05-09 nuevas features: USB C, boton encendido, conector touch,sin botones, sin NFC
2026-05-12 se fini
2026-05-13 agujeros tornillos
